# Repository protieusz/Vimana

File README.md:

# Vimana
A 40% Handwired Column Staggered Keeb with a 35mm Meshi Trackball Module in the middle in a shape of a Vimana.

What is a Vimana? As per https://en.wikipedia.org/wiki/Vimana, it is the following: 
"Vimāna are mythological flying palaces or chariots described in Hindu texts and Sanskrit epics. The "Pushpaka Vimana" of Ravana (who took it from Kubera; Rama returned it to Kubera) is the most quoted example of a vimana. Vimanas are also mentioned in Jain texts."

This is my interpretation of the Vimana keeb layout. BEHOLD!!! The VIMANA!

PCB version is untested and the bottom plate center Meshi trackball screw holes are off when tested during handwiring. Someone will need to use a digital caliper to fine tune the screw holes measurement.

Vimana Handwire Prototype Final

Ghetto bottom plate that needs screw adjustment. Hmm maybe the pcb bottom plate might need adjusting also

Handwiring

Handwiring the integrated Meshi Trackball module...the main prize

PCB Rev 1.0 Ready For Print.

Switch plate for pcb

Back plate for pcb

Meshi Trackball Module

Prototype

Key layout

Revised version 2.0 integrated switch plate case for handwiring

Revised version 2.0. Right Half done....waiting for other half to be printed

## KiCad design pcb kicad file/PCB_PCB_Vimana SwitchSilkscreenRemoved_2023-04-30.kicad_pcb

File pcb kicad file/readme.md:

The pcb file is converted from EasyEDA json file so I don't know how well it would work with KiCad.

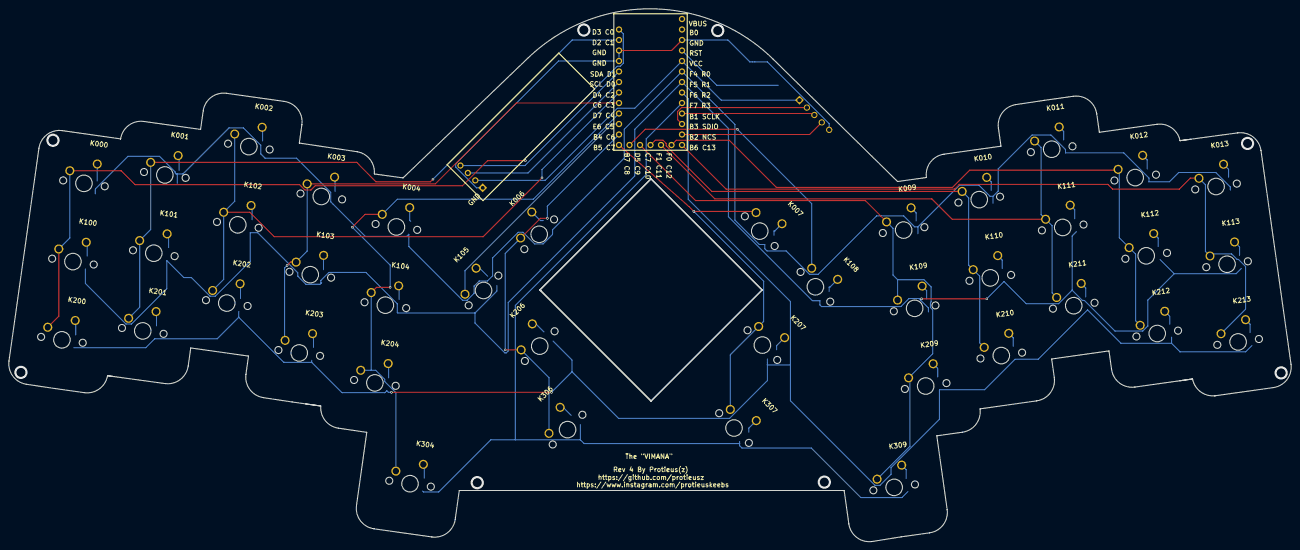
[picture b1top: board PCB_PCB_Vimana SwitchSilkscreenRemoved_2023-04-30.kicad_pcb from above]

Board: 2 copper layers, 310.2 x 128.9 mm, 84 parts (0 on the bottom side), 66 nets.

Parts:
D000, D001, D002, D003, D004, D006, D007, D009, D010, D011, D012, D013, D100, D101, D102, D103, D104, D105, D108, D109, D110, D111, D112, D113, D200, D201, D202, D203, D204, D206, D207, D209, D210, D211, D212, D213, D304, D306, D307, D309: DIODE-SOD123
J1: 5-Pin Male Header, 2.54mm Pitch, Thru-hole, squar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; 5-PIN_MALE_HEADER,_2.54MM_PITCH,_1.016MM_HOLE
K000, K001, K002, K003, K004, K006, K007, K009, K010, K011, K012, K013, K100, K101, K102, K103, K104, K105, K108, K109, K110, K111, K112, K113, K200, K201, K202, K203, K204, K206, K207, K209, K210, K211, K212, K213, K304, K306, K307, K309: 100; CHERRY_MX_100_MILLMAX
U1: ELITE-C
U2: OLED-091
U3: RESET SWITCH

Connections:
COL0: K000.2, K100.2, K200.2, U1.1
COL1: K001.2, K101.2, K201.2, U1.2
COL2: K002.2, K102.2, K202.2, U1.7
COL3: K003.2, K103.2, K203.2, U1.8
COL4: K004.2, K104.2, K204.2, K304.2, U1.9
COL5: K105.2, U1.10
COL6: K006.2, K206.2, K306.2, U1.11
COL7: K007.2, K207.2, K307.2, U1.12
COL8: K108.2, U1.13
COL9: K009.2, K109.2, K209.2, K309.2, U1.14
COL10: K010.2, K110.2, K210.2, U1.15
COL11: K011.2, K111.2, K211.2, U1.16
COL12: K012.2, K112.2, K212.2, U1.17
COL13: K013.2, K113.2, K213.2, U1.18
D001_A: D001.A, K001.1
D002_A: D002.A, K002.1
D004_A: D004.A, K004.1
D006_A: D006.A, K006.1
D007_A: D007.A, K007.1
D010_A: D010.A, K010.1
D012_A: D012.A, K012.1
D013_A: D013.A, K013.1
D100_A: D100.A, K100.1
D103_A: D103.A, K103.1
D105_A: D105.A, K105.1
D108_A: D108.A, K108.1
D109_A: D109.A, K109.1
D111_A: D111.A, K111.1
D113_A: D113.A, K113.1
D200_A: D200.A, K200.1
D203_A: D203.A, K203.1
D206_A: D206.A, K206.1
D207_A: D207.A, K207.1
D211_A: D211.A, K211.1
D213_A: D213.A, K213.1
D304_A: D304.A, K304.1
D306_A: D306.A, K306.1
D307_A: D307.A, K307.1
D309_A: D309.A, K309.1
GND: J1.5, U1.3, U1.4, U1.28, U2.GND, U3.2
K000_1: D000.A, K000.1
K003_1: D003.A, K003.1
K009_1: D009.A, K009.1
K011_1: D011.A, K011.1
K101_1: D101.A, K101.1
K102_1: D102.A, K102.1
K104_1: D104.A, K104.1
K110_1: D110.A, K110.1
K112_1: D112.A, K112.1
K201_1: D201.A, K201.1
K202_1: D202.A, K202.1
K204_1: D204.A, K204.1
K209_1: D209.A, K209.1
K210_1: D210.A, K210.1
K212_1: D212.A, K212.1
NCS: J1.4, U1.19
ROW0: D000.C, D001.C, D002.C, D003.C, D004.C, D006.C, D007.C, D009.C, D010.C, D011.C, D012.C, D013.C, U1.25
ROW1: D100.C, D101.C, D102.C, D103.C, D104.C, D105.C, D108.C, D109.C, D110.C, D111.C, D112.C, D113.C, U1.24
ROW2: D200.C, D201.C, D202.C, D203.C, D204.C, D206.C, D207.C, D209.C, D210.C, D211.C, D212.C, D213.C, U1.23
ROW3: D304.C, D306.C, D307.C, D309.C, U1.22
RST: U1.27, U3.1
SCL: U1.6, U2.SCL
SCLK: J1.3, U1.21
SDA: U1.5, U2.SDA
SDIO: J1.2, U1.20
VCC: J1.1, U1.26, U2.VCC

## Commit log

2023-03-21 Intro
2023-03-21 Added quotations in quote
2023-03-21 Add 2nd pic
2023-03-21 Create new
2023-03-21 Mistake
2023-03-21 Initial beta qmk upload
    Do not use since they are rough source codes, not final.
2023-03-21 Readme added
2023-03-21 Placeholder
2023-03-24 updated qmk
2023-03-24 screw up the files...uploading new one
2023-03-24 Updated qmk new upload
2023-03-24 Added case pic and key layout
2023-03-24 Change formatting
2023-04-07 Add 1 half pics
2023-04-07 Revised version 2.0 comment
2023-04-13 Add pcb rev 1 pic
2023-04-14 Add switch and backplate pics
2023-04-14 Alignment
2023-04-14 Edit titles
2023-04-14 Add more pcb colors
2023-04-14 Add Meshi trackball pics
2023-04-14 Add firmware
2023-04-23 Add QMK source code
2023-04-23 Update keyboard type
2023-04-23 Add 3D STL files for handwire and pcb base design
2023-04-23 Add Untested Rev4 Gerber pcb and plates
2023-04-23 Add final handwire pics
2023-04-23 Add the money shot pic
2023-04-24 Add scroll lock keycode
2023-04-24 Add readme for source code
2023-04-24 Add ready flash hex file
2023-04-24 Add readme
2023-04-24 Add warning
2023-04-24 Change final pic
2023-04-25 Add supplies list
2023-04-25 Add bullet formatting
2023-04-25 Changed formatting
2023-04-30 Add bottom plate pic
2023-04-30 pcb kicad file for Vimana for editing
2023-04-30 Schematic file added
2023-05-08 Screw holes update.
